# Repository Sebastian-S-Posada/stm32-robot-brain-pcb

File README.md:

# STM32 Robot Brain PCB

A custom controller board for a small mobile robot, designed in KiCad. It's built around an **STM32F103RCT6** microcontroller and brings together motor drive, sensor, Bluetooth, and programming connections on one 2-layer board.

## Features

- **MCU:** STM32F103RCT6 (ARM Cortex-M3, LQFP-64) with a 16 MHz crystal
- **Bluetooth:** MDBT42T-AT module (nRF52-based BLE)
- **USB:** Mini-B connector with USBLC6-2SC6 ESD protection and a resettable PTC fuse
- **Programming:** SWD header, plus BOOT and RESET switches
- **Sensor headers:** MPU6050 IMU and ultrasonic distance sensor
- **Robot I/O:** motor driver, Hall-effect encoders, track sensor, PS2 controller, and UART (JST-XH connectors)
- **Power:** separate 5 V and 3.3 V inputs, with power indicator LEDs
- **User I/O:** user button, user LED, Bluetooth status LED, and two RGB LEDs
- **Level shifting:** BSS138 MOSFET

## Images

| Top | Bottom |
|---|---|
|  |  |

The full schematic is in [images/schematic.pdf](images/schematic.pdf).

## Repository layout

```
hardware/
  *.kicad_pro / .kicad_sch / .kicad_pcb   KiCad project, schematic, and layout
  motor_controller.kicad_sch               Motor controller sub-sheet
  components/                              Custom symbols, footprints, and 3D models
  BOM/                                     Bill of materials (CSV)
  gerber/                                  Fabrication files (Gerbers and drill files)
images/                                    Renders and schematic PDF
```

## Opening the project

1. Install [KiCad](https://www.kicad.org/) (version 8 or newer).
2. Open `hardware/2025_04_STM32F103_RobotBrain.kicad_pro`.

To order boards, zip the contents of `hardware/gerber/` and upload them to a PCB fab such as JLCPCB or PCBWay.

## Context

Designed for an embedded systems course (ENCE 4231), spring 2025.

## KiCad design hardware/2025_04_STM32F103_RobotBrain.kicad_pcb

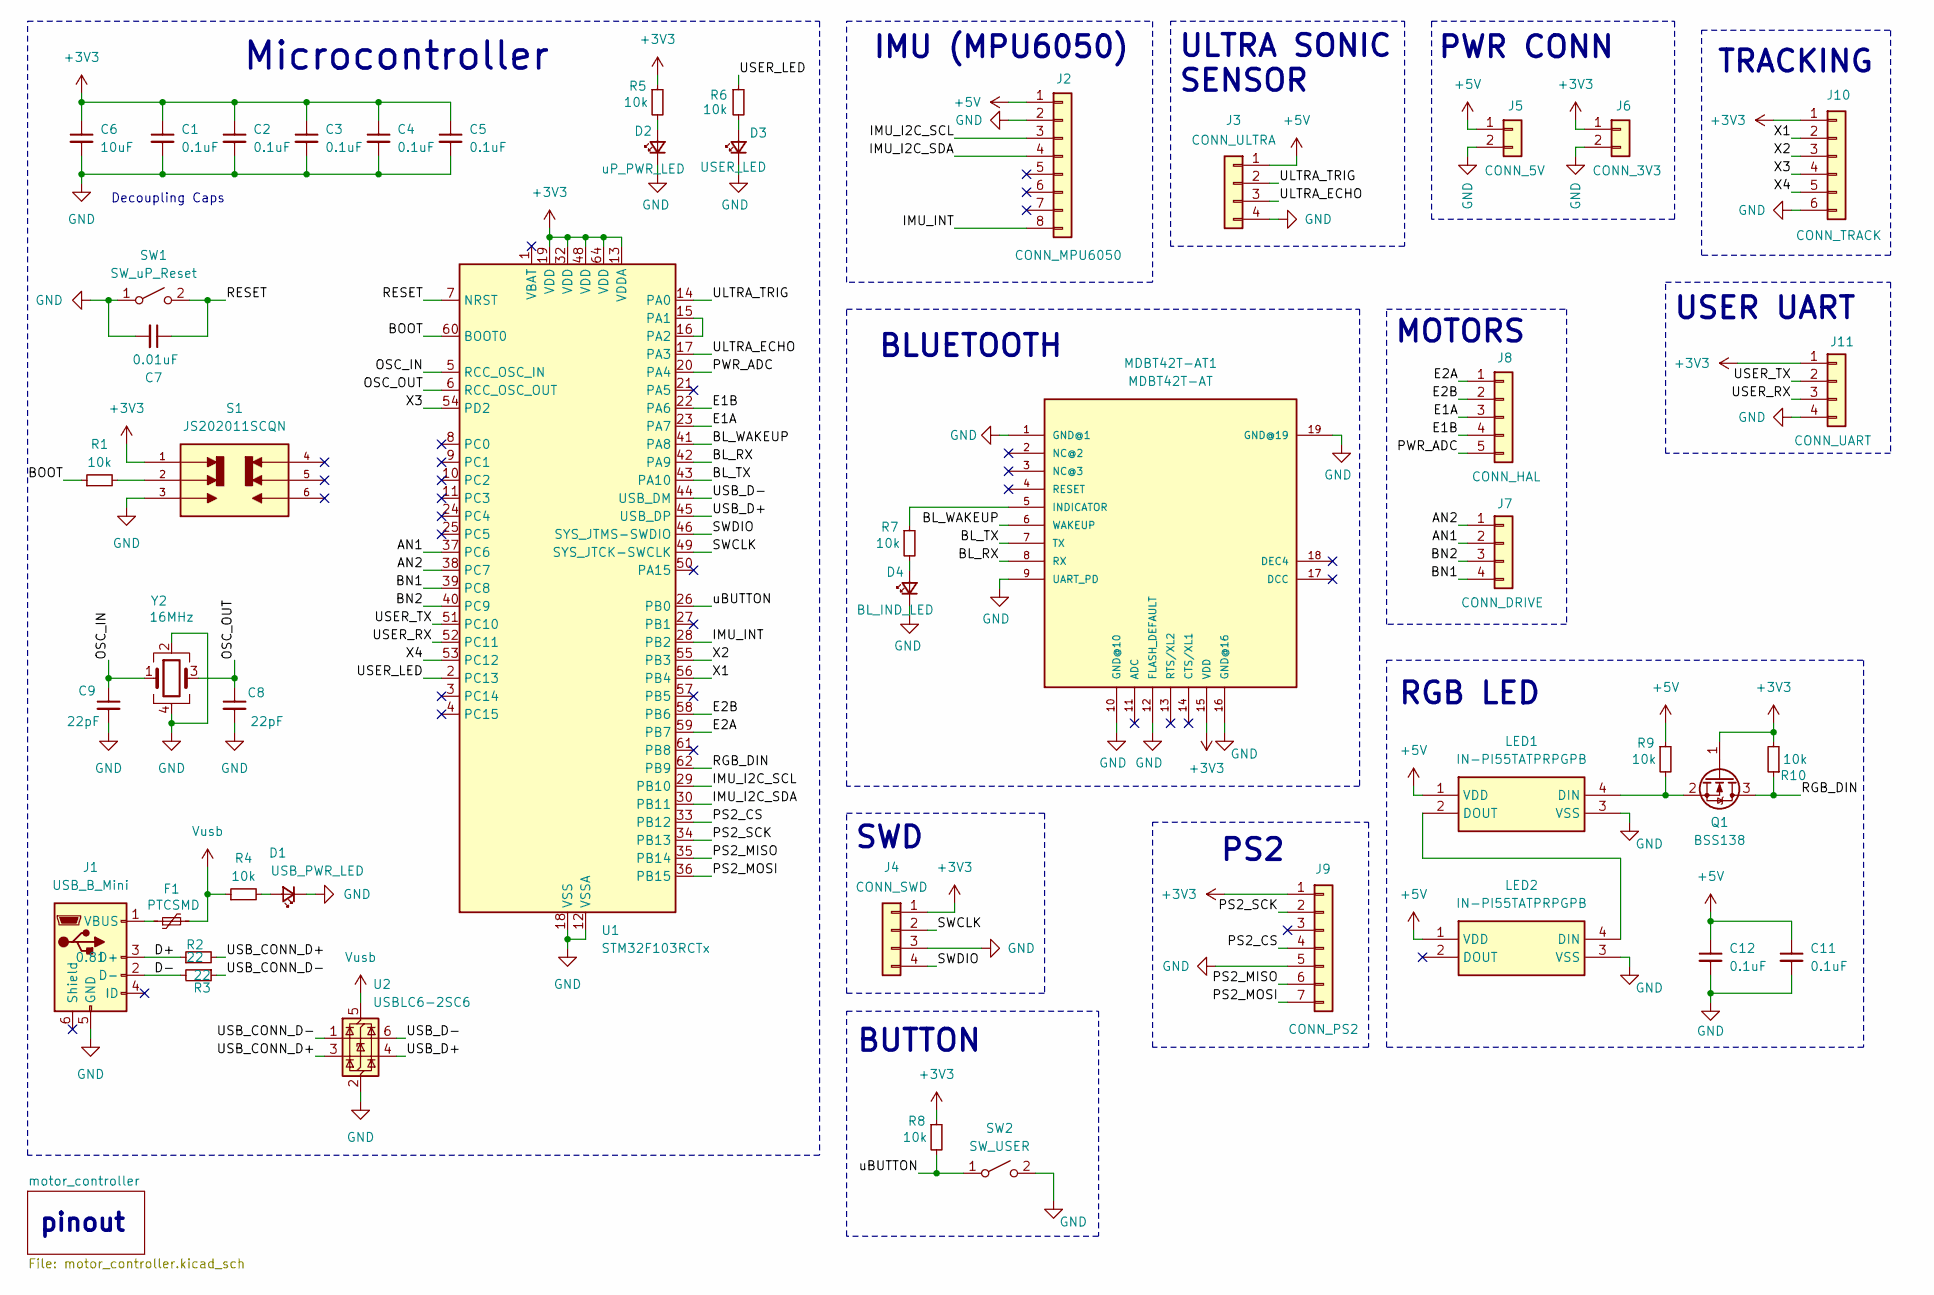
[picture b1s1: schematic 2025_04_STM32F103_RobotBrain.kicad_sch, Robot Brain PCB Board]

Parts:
C1, C2, C3, C4, C5, C11, C12: 0.1uF; C_0805_2012Metric_Pad1.18x1.45mm_HandSolder; Mfr #P KAM21BR71H104JT
C6: 10uF; C_0805_2012Metric_Pad1.18x1.45mm_HandSolder; Mfr #P LMK212ABJ106KG-T
C7: 0.01uF; C_0805_2012Metric_Pad1.18x1.45mm_HandSolder; Mfr #P KAF21BR72A103JT
C8, C9: 22pF; C_0805_2012Metric_Pad1.18x1.45mm_HandSolder; Mfr #P 0805ZA220JAT2A
D1: USB_PWR_LED; LED_0805_2012Metric_Pad1.15x1.40mm_HandSolder; Mfr #P 150080VS75000
D2: uP_PWR_LED; LED_0805_2012Metric_Pad1.15x1.40mm_HandSolder; Mfr #P 150080VS75000
D3: USER_LED; LED_0805_2012Metric_Pad1.15x1.40mm_HandSolder; Mfr #P 150080RS75000
D4: BL_IND_LED; LED_0805_2012Metric_Pad1.15x1.40mm_HandSolder; Mfr #P 150080VS75000
F1: PTCSMD; Fuse_0805_2012Metric_Pad1.15x1.40mm_HandSolder; Mfr #P 0ZCK0050AF2E
J1: USB_B_Mini; USB_Mini-B_Lumberg_2486_01_Horizontal; Mfr #P UJ2-MBH-4-SMT-TR
J2: CONN_MPU6050; PinSocket_1x08_P2.54mm_Vertical
J3: CONN_ULTRA; PinSocket_1x04_P2.54mm_Vertical
J4: CONN_SWD; PinSocket_1x04_P2.54mm_Vertical
J5: CONN_5V; JST_XH_B2B-XH-A_1x02_P2.50mm_Vertical
J6: CONN_3V3; JST_XH_B2B-XH-A_1x02_P2.50mm_Vertical
J7: CONN_DRIVE; JST_XH_B4B-XH-A_1x04_P2.50mm_Vertical
J8: CONN_HAL; JST_XH_B5B-XH-A_1x05_P2.50mm_Vertical
J9: CONN_PS2; PinHeader_1x07_P2.54mm_Vertical
J10: CONN_TRACK; JST_XH_B6B-XH-A_1x06_P2.50mm_Vertical
J11: CONN_UART; JST_XH_B4B-XH-A_1x04_P2.50mm_Vertical
LED1, LED2: IN-PI55TATPRPGPB; INPI55TATPRPGPB; Manufacturer_Part_Number IN-PI55TATPRPGPB; Mouser Part Number 743-IN-PI55TATPRPGPB
MDBT42T-AT1: MDBT42T-AT; MDBT42T
Q1: BSS138; SOT-23; Mfr #P BSS138
R1, R4, R5, R6, R7, R8, R9, R10: 10k; R_0805_2012Metric_Pad1.20x1.40mm_HandSolder; Mfr #P RK73B2ATTE103J
R2, R3: 22; R_0805_2012Metric_Pad1.20x1.40mm_HandSolder; Mfr #P RC0805FR-7W22RL
S1: JS202011SCQN; SW_uP_Boot; PARTREV 26 May 22
SW1: SW_uP_Reset; Mfr #P 434121025816
SW2: SW_USER; SW_SPST_PTS647_Sx50; Mfr #P TL3305BF100QG
U1: STM32F103RCTx; LQFP-64_10x10mm_P0.5mm; Mfr #P STM32F103RCT6
U2: USBLC6-2SC6; SOT-23-6; Mfr #P USBLC6-2SC6
Y2: 16MHz; Crystal_SMD_Abracon_ABM8G-4Pin_3.2x2.5mm; Mfr #P ABM8-16.000MHZ-D1X-T

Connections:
+3V3: C1.1, C2.1, C3.1, C4.1, C5.1, C6.1, J4.1, J6.1, J9.1, J10.1, J11.1, MDBT42T-AT1.15 (VDD), Q1.1 (G), R5.1, R8.1, R10.2, S1.1, U1.13 (VDDA), U1.19 (VDD), U1.32 (VDD), U1.48 (VDD), U1.64 (VDD)
+5V: C11.1, C12.1, J2.1, J3.1, J5.1, LED1.1 (VDD), LED2.1 (VDD), R9.1
/AN1: J7.2, U1.37 (PC6)
/AN2: J7.1, U1.38 (PC7)
/BL_RX: MDBT42T-AT1.8 (RX), U1.42 (PA9)
/BL_TX: MDBT42T-AT1.7 (TX), U1.43 (PA10)
/BL_WAKEUP: MDBT42T-AT1.6 (WAKEUP), U1.41 (PA8)
/BN1: J7.4, U1.39 (PC8)
/BN2: J7.3, U1.40 (PC9)
/BOOT: R1.1, U1.60 (BOOT0)
/D+: J1.3 (D+), R2.1
/D-: J1.2 (D-), R3.2
/E1A: J8.3, U1.23 (PA7)
/E1B: J8.4, U1.22 (PA6)
/E2A: J8.1, U1.59 (PB7)
/E2B: J8.2, U1.58 (PB6)
/IMU_I2C_SCL: J2.3, U1.29 (PB10)
/IMU_I2C_SDA: J2.4, U1.30 (PB11)
/IMU_INT: J2.8, U1.28 (PB2)
/OSC_IN: C9.1, U1.5 (RCC_OSC_IN), Y2.1
/OSC_OUT: C8.1, U1.6 (RCC_OSC_OUT), Y2.3
/PS2_CS: J9.4, U1.33 (PB12)
/PS2_MISO: J9.6, U1.35 (PB14)
/PS2_MOSI: J9.7, U1.36 (PB15)
/PS2_SCK: J9.2, U1.34 (PB13)
/PWR_ADC: J8.5, U1.20 (PA4)
/RESET: C7.1, SW1.2 (B), U1.7 (NRST)
/RGB_DIN: Q1.3 (D), R10.1, U1.62 (PB9)
/SWCLK: J4.2, U1.49 (SYS_JTCK-SWCLK)
/SWDIO: J4.4, U1.46 (SYS_JTMS-SWDIO)
/ULTRA_ECHO: J3.3, U1.17 (PA3)
/ULTRA_TRIG: J3.2, U1.14 (PA0)
/USB_CONN_D+: R2.2, U2.3 (I/O2)
/USB_CONN_D-: R3.1, U2.1 (I/O1)
/USB_D+: U1.45 (USB_DP), U2.4 (I/O2)
/USB_D-: U1.44 (USB_DM), U2.6 (I/O1)
/USER_LED: R6.1, U1.2 (PC13)
/USER_RX: J11.3, U1.52 (PC11)
/USER_TX: J11.2, U1.51 (PC10)
/X1: J10.2, U1.56 (PB4)
/X2: J10.3, U1.55 (PB3)
/X3: J10.4, U1.54 (PD2)
/X4: J10.5, U1.53 (PC12)
/uBUTTON: R8.2, SW2.1 (A), U1.26 (PB0)
GND: C1.2, C2.2, C3.2, C4.2, C5.2, C6.2, C7.2, C8.2, C9.2, C11.2, C12.2, D1.1 (K), D2.1 (K), D3.1 (K), D4.1 (K), J1.5 (GND), J2.2, J3.4, J4.3, J5.2, J6.2, J9.5, J10.6, J11.4, LED1.3 (VSS), LED2.3 (VSS), MDBT42T-AT1.1 (GND@1), MDBT42T-AT1.9 (UART_PD), MDBT42T-AT1.10 (GND@10), MDBT42T-AT1.12 (FLASH_DEFAULT), MDBT42T-AT1.16 (GND@16), MDBT42T-AT1.19 (GND@19), S1.3, SW1.1 (A), SW2.2 (B), U1.12 (VSSA), U1.18 (VSS), U1.31 (VSS), U1.47 (VSS), U1.63 (VSS), U2.2 (GND), Y2.2, Y2.4
unnamed: D1.2 (A), R4.2
unnamed: D2.2 (A), R5.2
unnamed: D3.2 (A), R6.2
unnamed: D4.2 (A), R7.2
unnamed: F1.1, J1.1 (VBUS)
unnamed: LED1.4 (DIN), Q1.2 (S), R9.2
unnamed: LED1.2 (DOUT), LED2.4 (DIN)
unnamed: MDBT42T-AT1.5 (INDICATOR), R7.1
unnamed: R1.2, S1.2
unnamed: U1.15 (PA1), U1.16 (PA2)
Vusb: F1.2, R4.1, U2.5 (VBUS)

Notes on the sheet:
PWR CONN
ULTRA SONIC SENSOR
Decoupling Caps
BUTTON
MOTORS
PS2
RGB LED
Microcontroller
TRACKING
pinout
IMU (MPU6050)
SWD
USER UART
BLUETOOTH

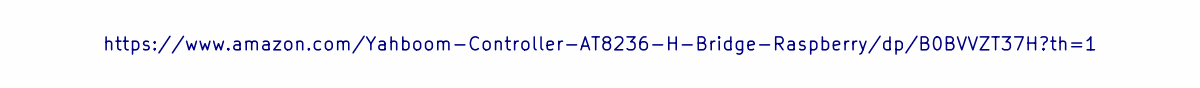
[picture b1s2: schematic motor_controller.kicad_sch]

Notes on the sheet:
https://www.amazon.com/Yahboom-Controller-AT8236-H-Bridge-Raspberry/dp/B0BVVZT37H?th=1

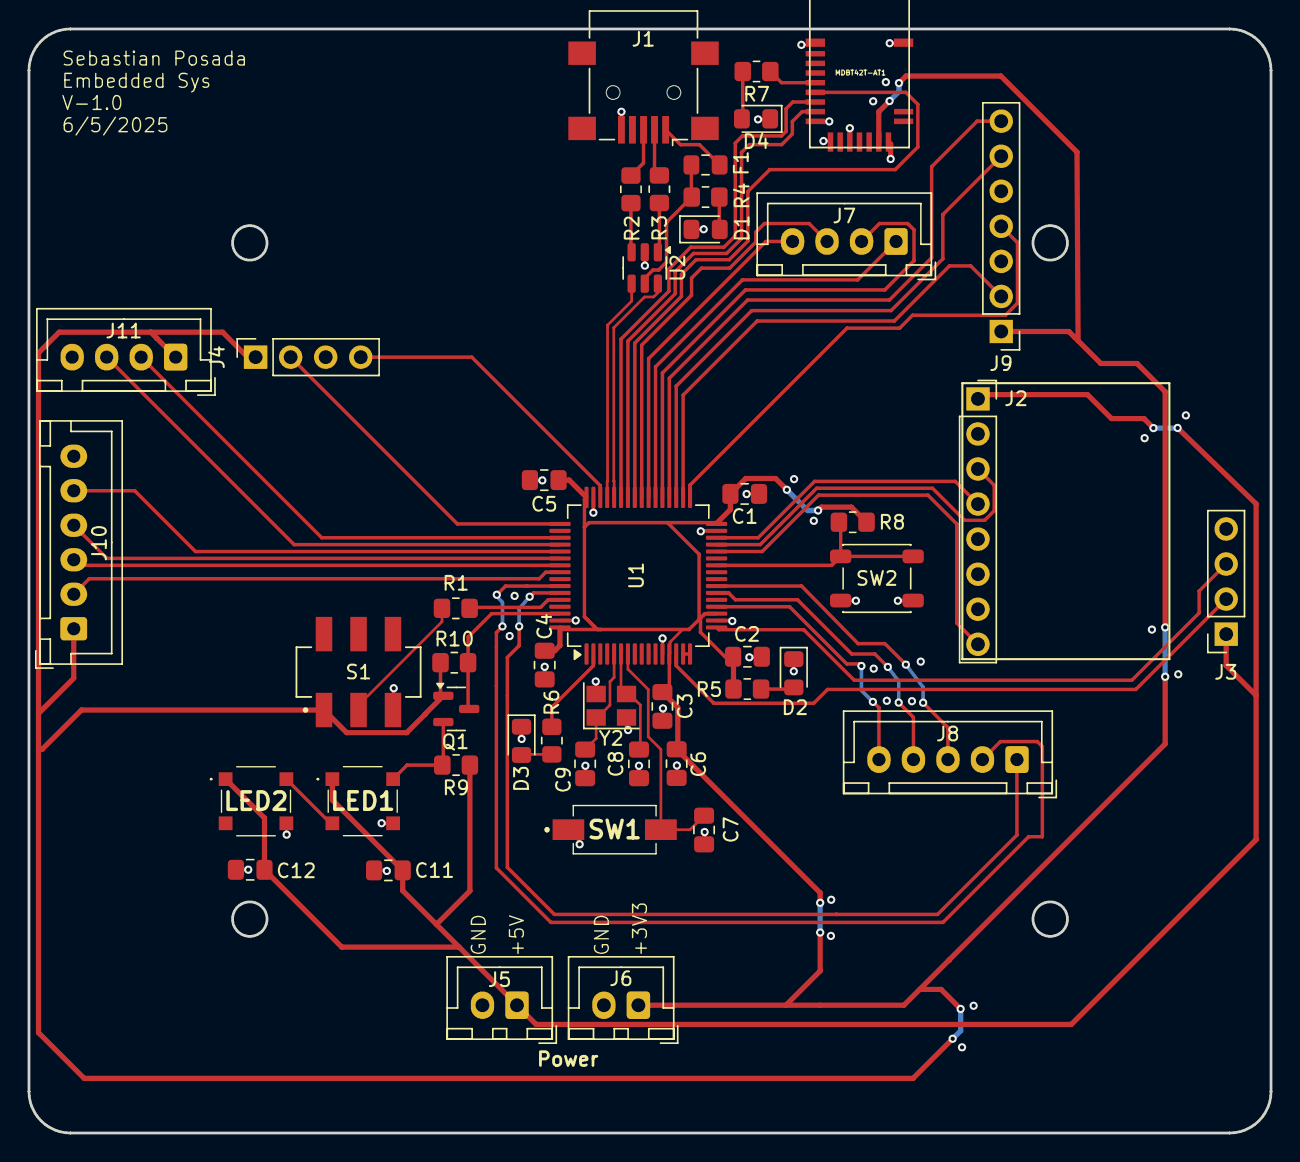
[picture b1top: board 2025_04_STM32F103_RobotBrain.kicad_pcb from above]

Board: 2 copper layers, 90.0 x 80.0 mm, 47 parts (0 on the bottom side), 56 nets.
